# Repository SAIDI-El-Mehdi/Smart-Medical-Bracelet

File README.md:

# Smart Medical Bracelet (IoT Health Monitor) 🩺⌚

An integrated mechatronics and IoT project focused on designing a wearable medical bracelet for continuous health monitoring. This project encompasses the full product development lifecycle, from system modeling to hardware design and mobile application deployment.

---

## 🚀 Key Engineering Dimensions

*   **Systems Engineering (SysML):** Comprehensive system architecture modeling (Requirements, Block Definition, and State Machine diagrams) to define functional relationships and data flow.
*   **Hardware Architecture (PCB Design - Eagle):** Custom printed circuit board design integrating vital sign sensors, power management, and wireless communication modules (IoT/Bluetooth).
*   **Mechanical & CAD Design (3D CAD):** Ergonomic and durable wearable casing designed for comfort, optimal sensor placement against the skin, and manufacturability.
*   **Software & Connectivity (Mobile App):** A dedicated companion mobile application developed to receive, process, and display real-time telemetry data from the bracelet.

---

## 📂 Repository Structure

The project is highly organized into the following engineering phases:

```text
Projet_Technique_Organise/
├── 01_Rapport/                  # Comprehensive project documentation and thesis reports
├── 02_Presentation/             # Slide decks and technical defense materials
├── 03_Code_Source/              # Firmware for the embedded microcontroller
├── 04_Simulation/               # System and physical simulations
├── 05_PCB_Eagle/                # PCB schematics and board layouts (Autodesk Eagle)
├── 06_Documentation/            # Datasheets and component references
├── 08_Conception_3D_CAD/        # Mechanical enclosure models and CAD assemblies
├── 09_Modelisation_SysML/       # System modeling diagrams (MBSE)
└── 10_Application_Mobile/       # Source code for the companion mobile application

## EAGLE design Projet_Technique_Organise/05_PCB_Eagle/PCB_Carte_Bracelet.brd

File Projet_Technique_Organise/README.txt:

Projet Technique - Bracelet Intelligent

Description generale
--------------------
Cette archive regroupe les elements principaux du projet technique relatif a la conception d'un bracelet intelligent de surveillance cardiaque et de detection de chute. Elle contient les livrables academiques, les fichiers de conception electronique, les codes sources, les simulations, la modelisation SysML, la conception 3D CAD, l'application mobile Flutter, ainsi que les documents de support.

Organisation du projet
----------------------
01_Rapport/
    Contient le rapport academique du projet et les documents rediges lies a la presentation technique du travail.

02_Presentation/
    Contient la presentation du projet destinee a l'expose oral ou a la soutenance.

03_Code_Source/
    Contient les codes sources utilises dans le projet, notamment les programmes embarques ou les fichiers de developpement logiciel.

04_Simulation/
    Contient les fichiers de simulation utilises pour tester le fonctionnement du systeme avant realisation ou integration.

05_PCB_Eagle/
    Contient les fichiers Autodesk Eagle relatifs a la conception electronique de la carte, ainsi que les versions PDF du schema electrique et du PCB.
    Fichiers principaux :
        - Schema_Electrique.pdf
        - PCB_Carte_Principale.pdf
        - Schema_Electronique_Bracelet.sch
        - PCB_Carte_Bracelet.brd
        - Configuration_Eagle.epf
        - CAM_Job_Bracelet_02.job
        - CAM_Job_Bracelet_03.job
        - CAM_Job_Bracelet_04.job
        - CAM_Job_Bracelet_05.job
        - Projet_Eagle_Bracelet_02.pro
        - Projet_Eagle_Bracelet_03.pro
        - Projet_Eagle_Bracelet_04.pro
        - Projet_Eagle_Bracelet_05.pro

06_Documentation/
    Contient les documents techniques, notices, references ou ressources utiles a la comprehension du projet.

07_Archives_ou_Doublons/
    Contient les anciens fichiers, sauvegardes, versions intermediaires ou elements conserves comme archives afin de ne rien supprimer du projet initial.

08_Conception_3D_CAD/
    Contient les fichiers de conception mecanique et de modelisation 3D, notamment les elements CAD du boitier ou du bracelet.

09_Modelisation_SysML/
    Contient les fichiers de modelisation systeme, diagrammes SysML ou elements d'analyse fonctionnelle du projet.

10_Application_Mobile_Flutter/
    Contient le projet de l'application mobile Flutter associee au bracelet intelligent.
    Ce dossier regroupe principalement :
        - lib/
        - assets/ si present
        - android/
        - ios/ si present
        - web/ si present
        - pubspec.yaml
        - pubspec.lock
        - analysis_options.yaml

Fichiers principaux
-------------------
- Rapport du projet : disponible dans 01_Rapport/
- Presentation du projet : disponible dans 02_Presentation/
- Code source embarque : disponible dans 03_Code_Source/
- Simulation : disponible dans 04_Simulation/
- Schema electrique PDF : 05_PCB_Eagle/Schema_Electrique.pdf
- PCB PDF : 05_PCB_Eagle/PCB_Carte_Principale.pdf
- Schema Eagle : 05_PCB_Eagle/Schema_Electronique_Bracelet.sch
- Carte PCB Eagle : 05_PCB_Eagle/PCB_Carte_Bracelet.brd
- Conception 3D : disponible dans 08_Conception_3D_CAD/
- Modelisation SysML : disponible dans 09_Modelisation_SysML/
- Application mobile Flutter : disponible dans 10_Application_Mobile_Flutter/

Remarques
---------
- Les fichiers originaux du projet ont ete conserves dans leurs dossiers respectifs.
- Les fichiers de sauvegarde, versions intermediaires ou doublons sont regroupes dans 07_Archives_ou_Doublons/.
- Le schema electrique et le PCB sont regroupes dans le meme dossier 05_PCB_Eagle/ afin de garder ensemble tous les elements de conception electronique.
- L'application Flutter est placee dans 10_Application_Mobile_Flutter/ pour separer clairement la partie mobile du reste du projet technique.
- Les fichiers generes automatiquement par Flutter ou Gradle, comme build/, .dart_tool/ et .gradle/, ne sont pas necessaires pour la presentation academique et peuvent etre regeneres avec les commandes flutter pub get et flutter run.
- Les noms des dossiers sont numerotes pour faciliter la consultation et la presentation academique du projet.
- Aucun contenu interne des fichiers techniques n'a ete modifie.

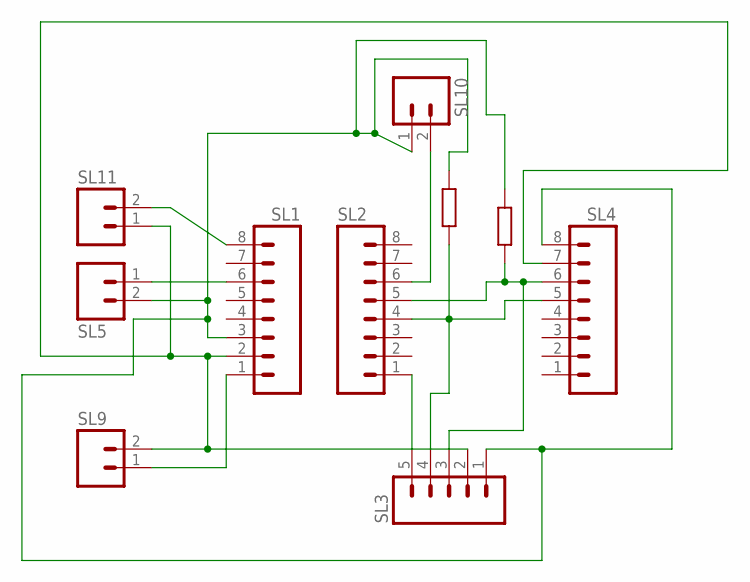
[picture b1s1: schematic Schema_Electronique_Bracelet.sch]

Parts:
SL1: ESP32_LEFT; 08PA
SL2: ESP32_RIGHT; 08PA
SL3: MAX30102; 05PA
SL4: MPU6050; 08PA
SL5: BUZZER; 02PA
SL9: ON_OFF_SWITCH; 02PA
SL10, SL11: POWER_INPUT; 02PA

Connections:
LED: SL1.2, SL3.2, SL4.7, SL9.2, SL11.1
unnamed: SL1.8, SL11.2
unnamed: SL1.1, SL9.1
unnamed: SL1.6, SL5.1
unnamed: SL1.3, SL3.1, SL4.8, SL5.2, SL10.1
unnamed: SL2.6, SL10.2
unnamed: SL2.1, SL3.5
NC_MPU_XCL: SL2.5, SL3.3, SL4.6
NC_MPU_XDA: SL2.4, SL3.4, SL4.5

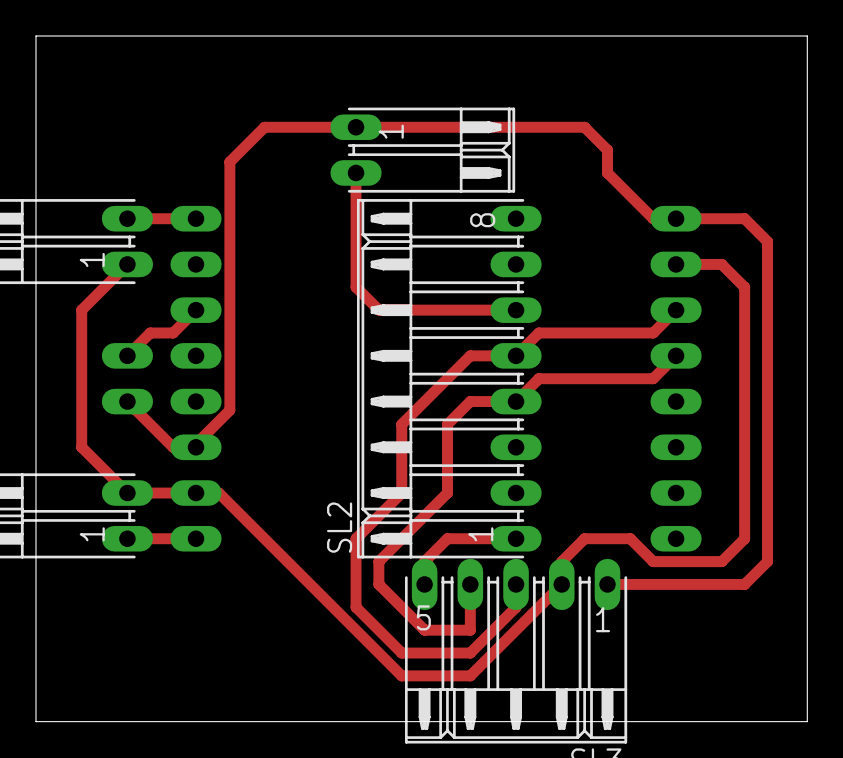
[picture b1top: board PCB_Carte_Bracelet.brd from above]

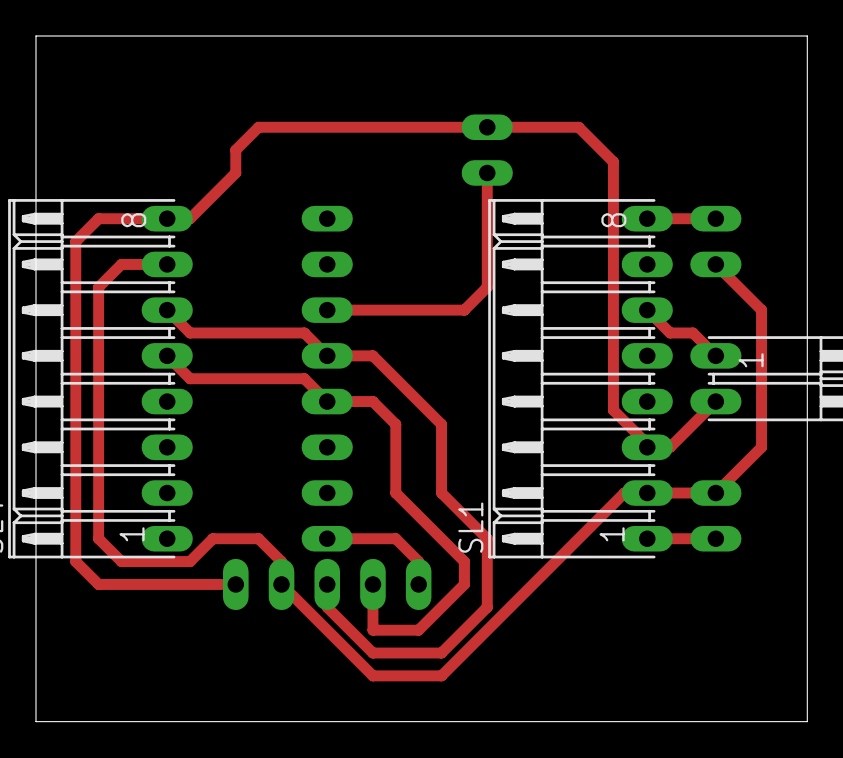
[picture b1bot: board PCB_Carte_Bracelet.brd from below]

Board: 2 copper layers, 42.9 x 38.1 mm, 8 parts (3 on the bottom side), 9 nets.
